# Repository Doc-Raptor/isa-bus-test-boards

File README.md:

# isa-bus-test-boards for building isa-bus-cards

not tested

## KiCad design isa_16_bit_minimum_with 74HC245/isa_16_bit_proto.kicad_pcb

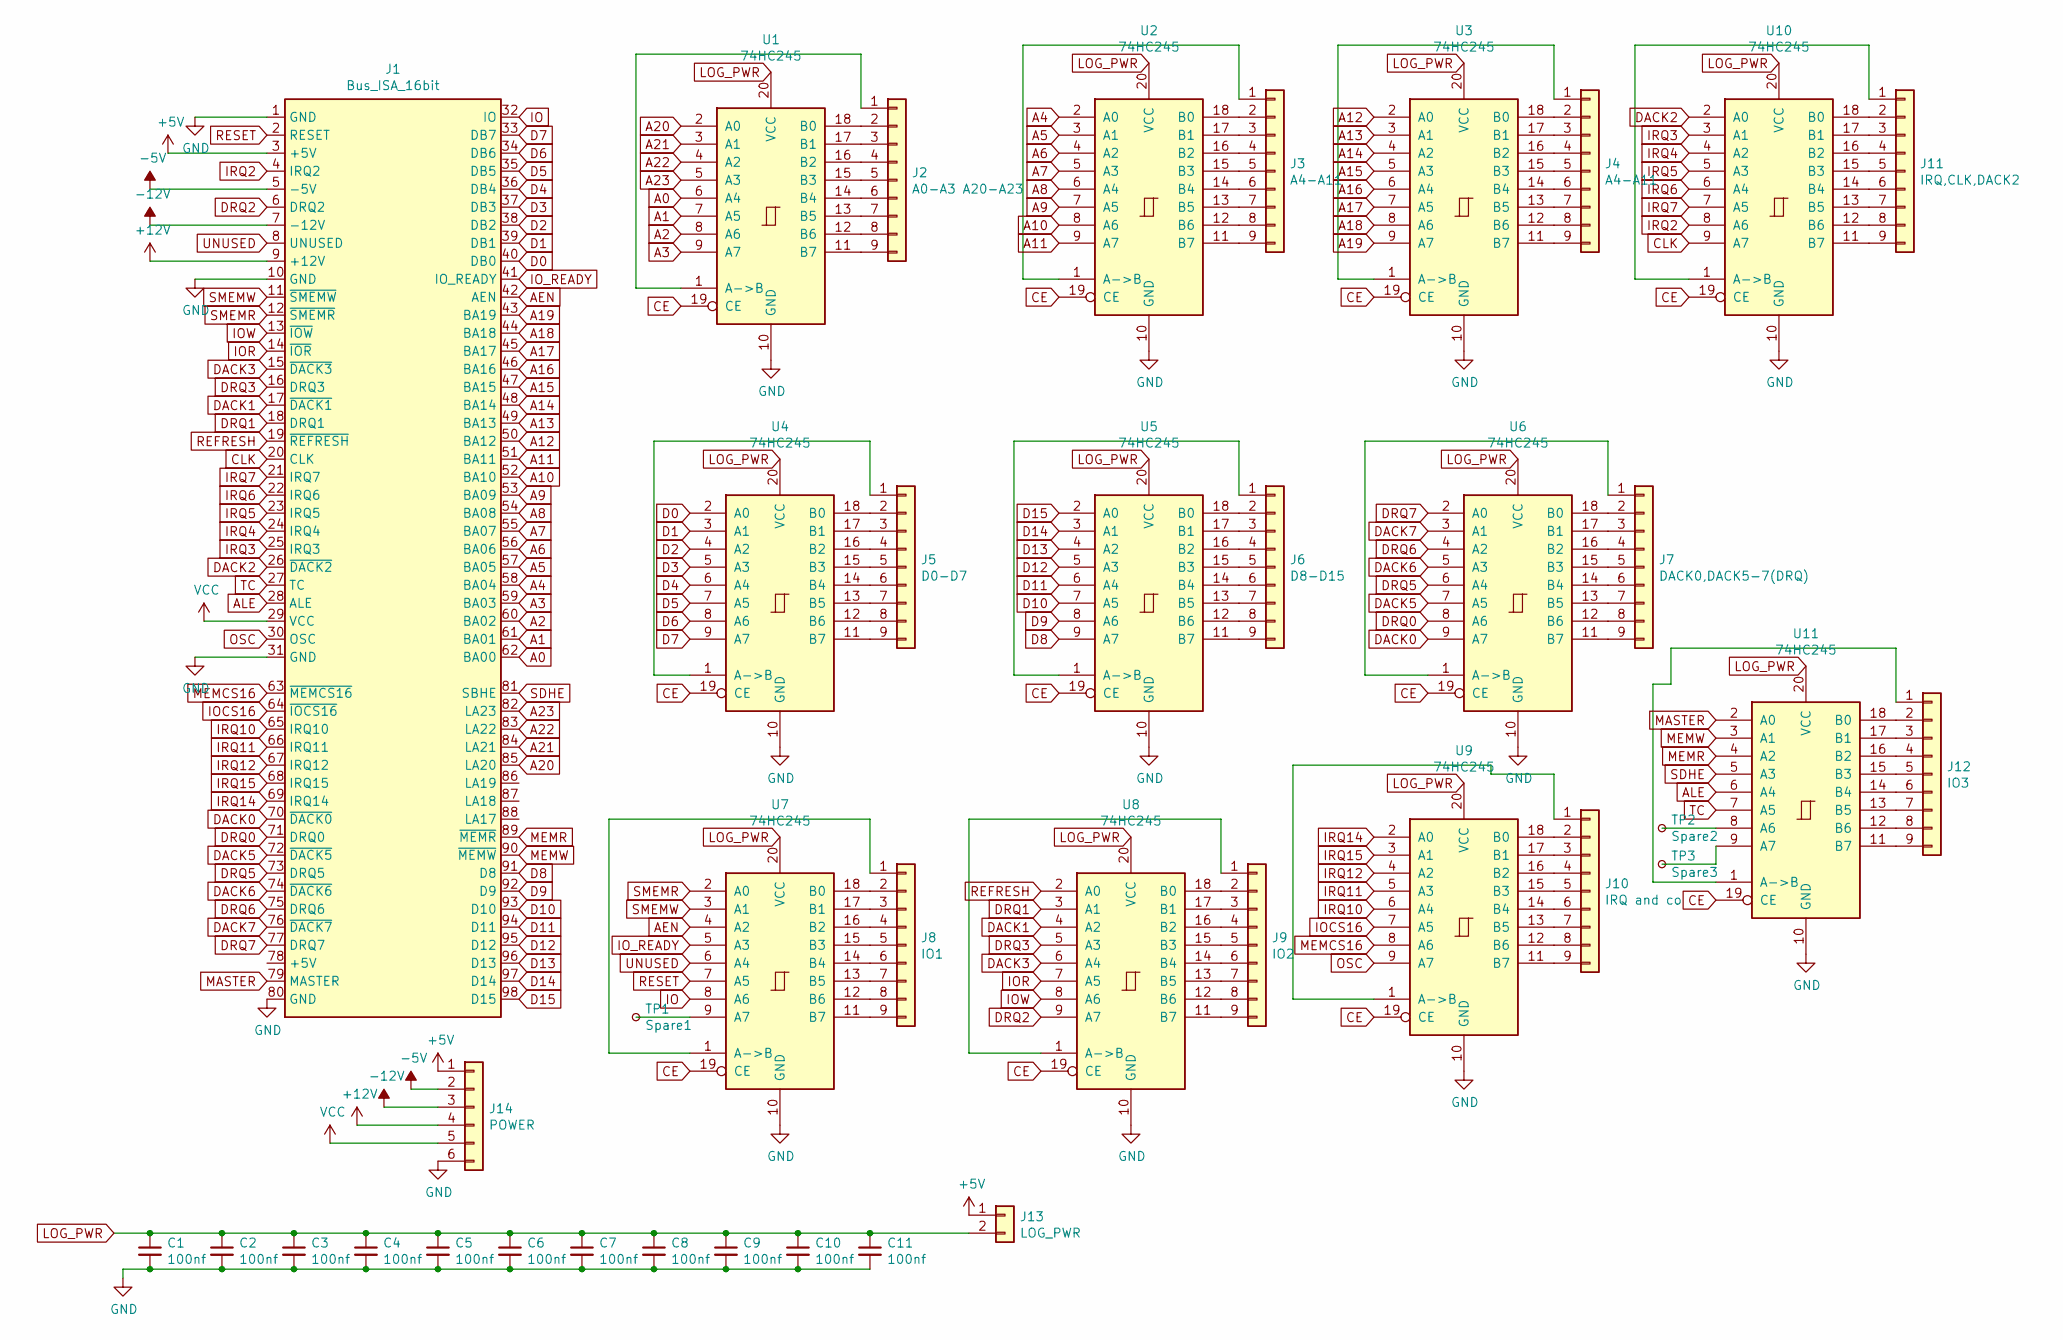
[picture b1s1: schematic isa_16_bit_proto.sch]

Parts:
C1, C2, C3, C4, C5, C6, C7, C8, C9, C10, C11: 100nf; C_Disc_D6.0mm_W2.5mm_P5.00mm
J1: Bus_ISA_16bit; BUS_AT
J2: A0-A3 A20-A23; PinHeader_1x09_P2.54mm_Vertical
J3, J4: A4-A11; PinHeader_1x09_P2.54mm_Vertical
J5: D0-D7; PinHeader_1x09_P2.54mm_Vertical
J6: D8-D15; PinHeader_1x09_P2.54mm_Vertical
J7: DACK0,DACK5-7(DRQ); PinHeader_1x09_P2.54mm_Vertical
J8: IO1; PinHeader_1x09_P2.54mm_Vertical
J9: IO2; PinHeader_1x09_P2.54mm_Vertical
J10: IRQ and co; PinHeader_1x09_P2.54mm_Vertical
J11: IRQ,CLK,DACK2; PinHeader_1x09_P2.54mm_Vertical
J12: IO3; PinHeader_1x09_P2.54mm_Vertical
J13: LOG_PWR; PinHeader_1x02_P2.54mm_Vertical
J14: POWER; PinHeader_1x06_P2.54mm_Vertical
TP1: Spare1; TestPoint_Pad_D1.0mm
TP2: Spare2; TestPoint_Pad_D1.0mm
TP3: Spare3; TestPoint_Pad_D1.0mm
U1, U2, U3, U4, U5, U6, U7, U8, U9, U10, U11: 74HC245; DIP-20_W7.62mm_Socket

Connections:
+5V: J1.3 (+5V), J13.1, J14.1
+12V: J1.9 (+12V), J14.4
-5V: J1.5 (-5V), J14.2
-12V: J1.7 (-12V), J14.3
A0: J1.62 (BA00), U1.6 (A4)
A1: J1.61 (BA01), U1.7 (A5)
A2: J1.60 (BA02), U1.8 (A6)
A3: J1.59 (BA03), U1.9 (A7)
A4: J1.58 (BA04), U2.2 (A0)
A5: J1.57 (BA05), U2.3 (A1)
A6: J1.56 (BA06), U2.4 (A2)
A7: J1.55 (BA07), U2.5 (A3)
A8: J1.54 (BA08), U2.6 (A4)
A9: J1.53 (BA09), U2.7 (A5)
A10: J1.52 (BA10), U2.8 (A6)
A11: J1.51 (BA11), U2.9 (A7)
A12: J1.50 (BA12), U3.2 (A0)
A13: J1.49 (BA13), U3.3 (A1)
A14: J1.48 (BA14), U3.4 (A2)
A15: J1.47 (BA15), U3.5 (A3)
A16: J1.46 (BA16), U3.6 (A4)
A17: J1.45 (BA17), U3.7 (A5)
A18: J1.44 (BA18), U3.8 (A6)
A19: J1.43 (BA19), U3.9 (A7)
A20: J1.85 (LA20), U1.2 (A0)
A21: J1.84 (LA21), U1.3 (A1)
A22: J1.83 (LA22), U1.4 (A2)
A23: J1.82 (LA23), U1.5 (A3)
AEN: J1.42 (AEN), U7.4 (A2)
ALE: J1.28 (ALE), U11.6 (A4)
CE: U1.19 (CE), U2.19 (CE), U3.19 (CE), U4.19 (CE), U5.19 (CE), U6.19 (CE), U7.19 (CE), U8.19 (CE), U9.19 (CE), U10.19 (CE), U11.19 (CE)
CLK: J1.20 (CLK), U10.9 (A7)
D0: J1.40 (DB0), U4.2 (A0)
D1: J1.39 (DB1), U4.3 (A1)
D2: J1.38 (DB2), U4.4 (A2)
D3: J1.37 (DB3), U4.5 (A3)
D4: J1.36 (DB4), U4.6 (A4)
D5: J1.35 (DB5), U4.7 (A5)
D6: J1.34 (DB6), U4.8 (A6)
D7: J1.33 (DB7), U4.9 (A7)
D8: J1.91 (D8), U5.9 (A7)
D9: J1.92 (D9), U5.8 (A6)
D10: J1.93 (D10), U5.7 (A5)
D11: J1.94 (D11), U5.6 (A4)
D12: J1.95 (D12), U5.5 (A3)
D13: J1.96 (D13), U5.4 (A2)
D14: J1.97 (D14), U5.3 (A1)
D15: J1.98 (D15), U5.2 (A0)
DACK0: J1.70 (~DACK0), U6.9 (A7)
DACK1: J1.17 (~DACK1), U8.4 (A2)
DACK2: J1.26 (~DACK2), U10.2 (A0)
DACK3: J1.15 (~DACK3), U8.6 (A4)
DACK5: J1.72 (~DACK5), U6.7 (A5)
DACK6: J1.74 (~DACK6), U6.5 (A3)
DACK7: J1.76 (~DACK7), U6.3 (A1)
DRQ0: J1.71 (DRQ0), U6.8 (A6)
DRQ1: J1.18 (DRQ1), U8.3 (A1)
DRQ2: J1.6 (DRQ2), U8.9 (A7)
DRQ3: J1.16 (DRQ3), U8.5 (A3)
DRQ5: J1.73 (DRQ5), U6.6 (A4)
DRQ6: J1.75 (DRQ6), U6.4 (A2)
DRQ7: J1.77 (DRQ7), U6.2 (A0)
GND: C1.2, C2.2, C3.2, C4.2, C5.2, C6.2, C7.2, C8.2, C9.2, C10.2, C11.2, J1.1 (GND), J1.10 (GND), J1.31 (GND), J1.80 (GND), J14.6, U1.10 (GND), U2.10 (GND), U3.10 (GND), U4.10 (GND), U5.10 (GND), U6.10 (GND), U7.10 (GND), U8.10 (GND), U9.10 (GND), U10.10 (GND), U11.10 (GND)
IO: J1.32 (IO), U7.8 (A6)
IOCS16: J1.64 (~IOCS16), U9.7 (A5)
IOR: J1.14 (~IOR), U8.7 (A5)
IOW: J1.13 (~IOW), U8.8 (A6)
IO_READY: J1.41 (IO_READY), U7.5 (A3)
IRQ2: J1.4 (IRQ2), U10.8 (A6)
IRQ3: J1.25 (IRQ3), U10.3 (A1)
IRQ4: J1.24 (IRQ4), U10.4 (A2)
IRQ5: J1.23 (IRQ5), U10.5 (A3)
IRQ6: J1.22 (IRQ6), U10.6 (A4)
IRQ7: J1.21 (IRQ7), U10.7 (A5)
IRQ10: J1.65 (IRQ10), U9.6 (A4)
IRQ11: J1.66 (IRQ11), U9.5 (A3)
IRQ12: J1.67 (IRQ12), U9.4 (A2)
IRQ14: J1.69 (IRQ14), U9.2 (A0)
IRQ15: J1.68 (IRQ15), U9.3 (A1)
LOG_PWR: C1.1, C2.1, C3.1, C4.1, C5.1, C6.1, C7.1, C8.1, C9.1, C10.1, C11.1, J13.2, U1.20 (VCC), U2.20 (VCC), U3.20 (VCC), U4.20 (VCC), U5.20 (VCC), U6.20 (VCC), U7.20 (VCC), U8.20 (VCC), U9.20 (VCC), U10.20 (VCC), U11.20 (VCC)
MASTER: J1.79 (MASTER), U11.2 (A0)
MEMCS16: J1.63 (~MEMCS16), U9.8 (A6)
MEMR: J1.89 (~MEMR), U11.4 (A2)
MEMW: J1.90 (~MEMW), U11.3 (A1)
unnamed: J2.1, U1.1 (A->B)
unnamed: J2.2, U1.18 (B0)
unnamed: J2.3, U1.17 (B1)
unnamed: J2.4, U1.16 (B2)
unnamed: J2.5, U1.15 (B3)
unnamed: J2.6, U1.14 (B4)
unnamed: J2.7, U1.13 (B5)
unnamed: J2.8, U1.12 (B6)
unnamed: J2.9, U1.11 (B7)
unnamed: J3.1, U2.1 (A->B)
unnamed: J3.2, U2.18 (B0)
unnamed: J3.3, U2.17 (B1)
unnamed: J3.4, U2.16 (B2)
unnamed: J3.5, U2.15 (B3)
unnamed: J3.6, U2.14 (B4)
unnamed: J3.7, U2.13 (B5)
unnamed: J3.8, U2.12 (B6)
unnamed: J3.9, U2.11 (B7)
unnamed: J4.1, U3.1 (A->B)
unnamed: J4.2, U3.18 (B0)
unnamed: J4.3, U3.17 (B1)
unnamed: J4.4, U3.16 (B2)
unnamed: J4.5, U3.15 (B3)
unnamed: J4.6, U3.14 (B4)
unnamed: J4.7, U3.13 (B5)
unnamed: J4.8, U3.12 (B6)
unnamed: J4.9, U3.11 (B7)
unnamed: J5.1, U4.1 (A->B)
unnamed: J5.2, U4.18 (B0)
unnamed: J5.3, U4.17 (B1)
unnamed: J5.4, U4.16 (B2)
unnamed: J5.5, U4.15 (B3)
unnamed: J5.6, U4.14 (B4)
unnamed: J5.7, U4.13 (B5)
unnamed: J5.8, U4.12 (B6)
unnamed: J5.9, U4.11 (B7)
unnamed: J6.1, U5.1 (A->B)
unnamed: J6.2, U5.18 (B0)
unnamed: J6.3, U5.17 (B1)
unnamed: J6.4, U5.16 (B2)
unnamed: J6.5, U5.15 (B3)
unnamed: J6.6, U5.14 (B4)
unnamed: J6.7, U5.13 (B5)
unnamed: J6.8, U5.12 (B6)
unnamed: J6.9, U5.11 (B7)
unnamed: J7.1, U6.1 (A->B)
unnamed: J7.2, U6.18 (B0)
unnamed: J7.3, U6.17 (B1)
unnamed: J7.4, U6.16 (B2)
unnamed: J7.5, U6.15 (B3)
unnamed: J7.6, U6.14 (B4)
unnamed: J7.7, U6.13 (B5)
unnamed: J7.8, U6.12 (B6)
unnamed: J7.9, U6.11 (B7)
unnamed: J8.1, U7.1 (A->B)
unnamed: J8.2, U7.18 (B0)
unnamed: J8.3, U7.17 (B1)
unnamed: J8.4, U7.16 (B2)
unnamed: J8.5, U7.15 (B3)
unnamed: J8.6, U7.14 (B4)
unnamed: J8.7, U7.13 (B5)
unnamed: J8.8, U7.12 (B6)
unnamed: J8.9, U7.11 (B7)
unnamed: J9.1, U8.1 (A->B)
unnamed: J9.2, U8.18 (B0)
unnamed: J9.3, U8.17 (B1)
unnamed: J9.4, U8.16 (B2)
unnamed: J9.5, U8.15 (B3)
unnamed: J9.6, U8.14 (B4)
unnamed: J9.7, U8.13 (B5)
unnamed: J9.8, U8.12 (B6)
unnamed: J9.9, U8.11 (B7)
unnamed: J10.1, U9.1 (A->B)
unnamed: J10.2, U9.18 (B0)
unnamed: J10.3, U9.17 (B1)
unnamed: J10.4, U9.16 (B2)
unnamed: J10.5, U9.15 (B3)
unnamed: J10.6, U9.14 (B4)
unnamed: J10.7, U9.13 (B5)
unnamed: J10.8, U9.12 (B6)
unnamed: J10.9, U9.11 (B7)
unnamed: J11.1, U10.1 (A->B)
unnamed: J11.2, U10.18 (B0)
unnamed: J11.3, U10.17 (B1)
unnamed: J11.4, U10.16 (B2)
unnamed: J11.5, U10.15 (B3)
unnamed: J11.6, U10.14 (B4)
unnamed: J11.7, U10.13 (B5)
unnamed: J11.8, U10.12 (B6)
unnamed: J11.9, U10.11 (B7)
unnamed: J12.1, U11.1 (A->B)
unnamed: J12.2, U11.18 (B0)
unnamed: J12.3, U11.17 (B1)
unnamed: J12.4, U11.16 (B2)
unnamed: J12.5, U11.15 (B3)
unnamed: J12.6, U11.14 (B4)
unnamed: J12.7, U11.13 (B5)
unnamed: J12.8, U11.12 (B6)
unnamed: J12.9, U11.11 (B7)
unnamed: TP1.1, U7.9 (A7)
unnamed: TP2.1, U11.8 (A6)
unnamed: TP3.1, U11.9 (A7)
OSC: J1.30 (OSC), U9.9 (A7)
REFRESH: J1.19 (~REFRESH), U8.2 (A0)
RESET: J1.2 (RESET), U7.7 (A5)
SDHE: J1.81 (SBHE), U11.5 (A3)
SMEMR: J1.12 (~SMEMR), U7.2 (A0)
SMEMW: J1.11 (~SMEMW), U7.3 (A1)
TC: J1.27 (TC), U11.7 (A5)
UNUSED: J1.8 (UNUSED), U7.6 (A4)
VCC: J1.29 (VCC), J14.5

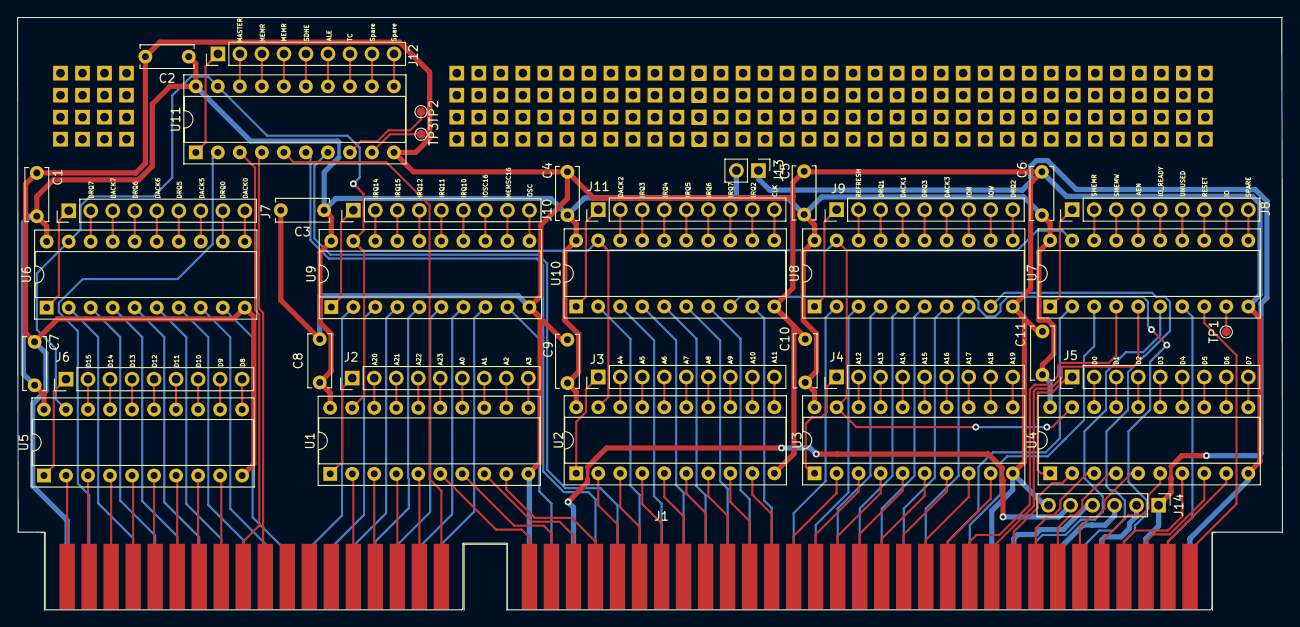
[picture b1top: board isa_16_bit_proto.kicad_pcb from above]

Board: 2 copper layers, 145.9 x 68.3 mm, 39 parts (0 on the bottom side), 195 nets.

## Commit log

2021-04-07 Added files
